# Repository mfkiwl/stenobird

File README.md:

# stenobird
a wip, unnamed stenographic keyboard family.
currently in a heavy WIP stage, with the repository acting as simple VC over the yamls and PCBs

## Design Considerations
The stenobird family aims to provide a **choc-spaced** and **variably choc min spaced** 222222+3 layout for stenography and standard typing.

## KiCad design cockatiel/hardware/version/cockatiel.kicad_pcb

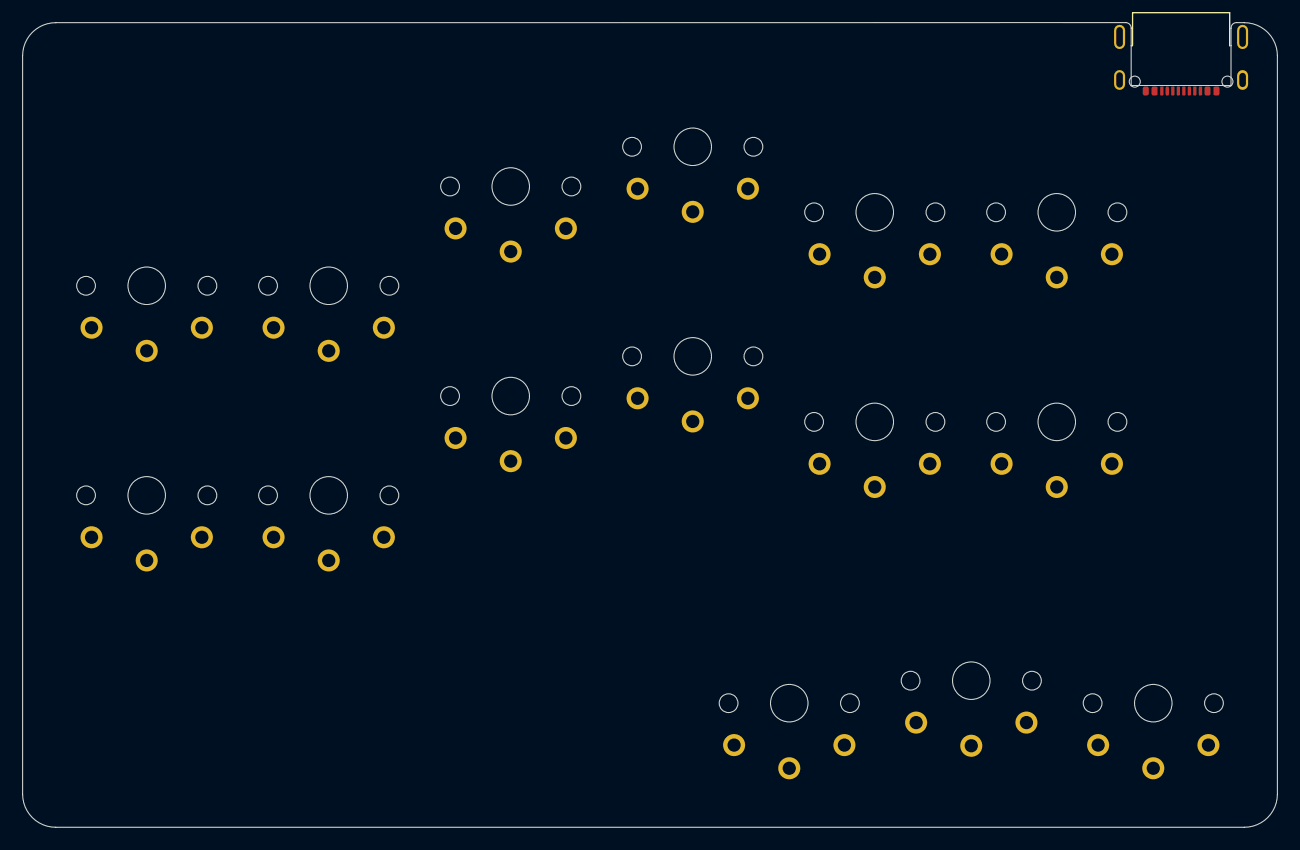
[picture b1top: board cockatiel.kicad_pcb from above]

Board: 4 copper layers, 113.8 x 72.9 mm, 17 parts (1 on the bottom side), 3 nets, no tracks yet.

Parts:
J1: USB_C_Receptacle_USB2.0; USB-C_MID_MOUNT_918-418K2024S40000
LOGO2: Logo_Open_Hardware_Small; OSHW_Logo_3.6x3.6_F.Mask
S1, S2, S3, S4, S5, S6, S7, S8, S9, S10, S11, S12, S13, S14, S15: pg1350-RS

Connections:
/USB+: J1.A6 (D+), J1.B6 (D+)
/USB-: J1.A7 (D-), J1.B7 (D-)
GND: J1.A1 (GND), J1.S1 (SHIELD), J1.S2 (SHIELD), J1.S3 (SHIELD), J1.S4 (SHIELD)

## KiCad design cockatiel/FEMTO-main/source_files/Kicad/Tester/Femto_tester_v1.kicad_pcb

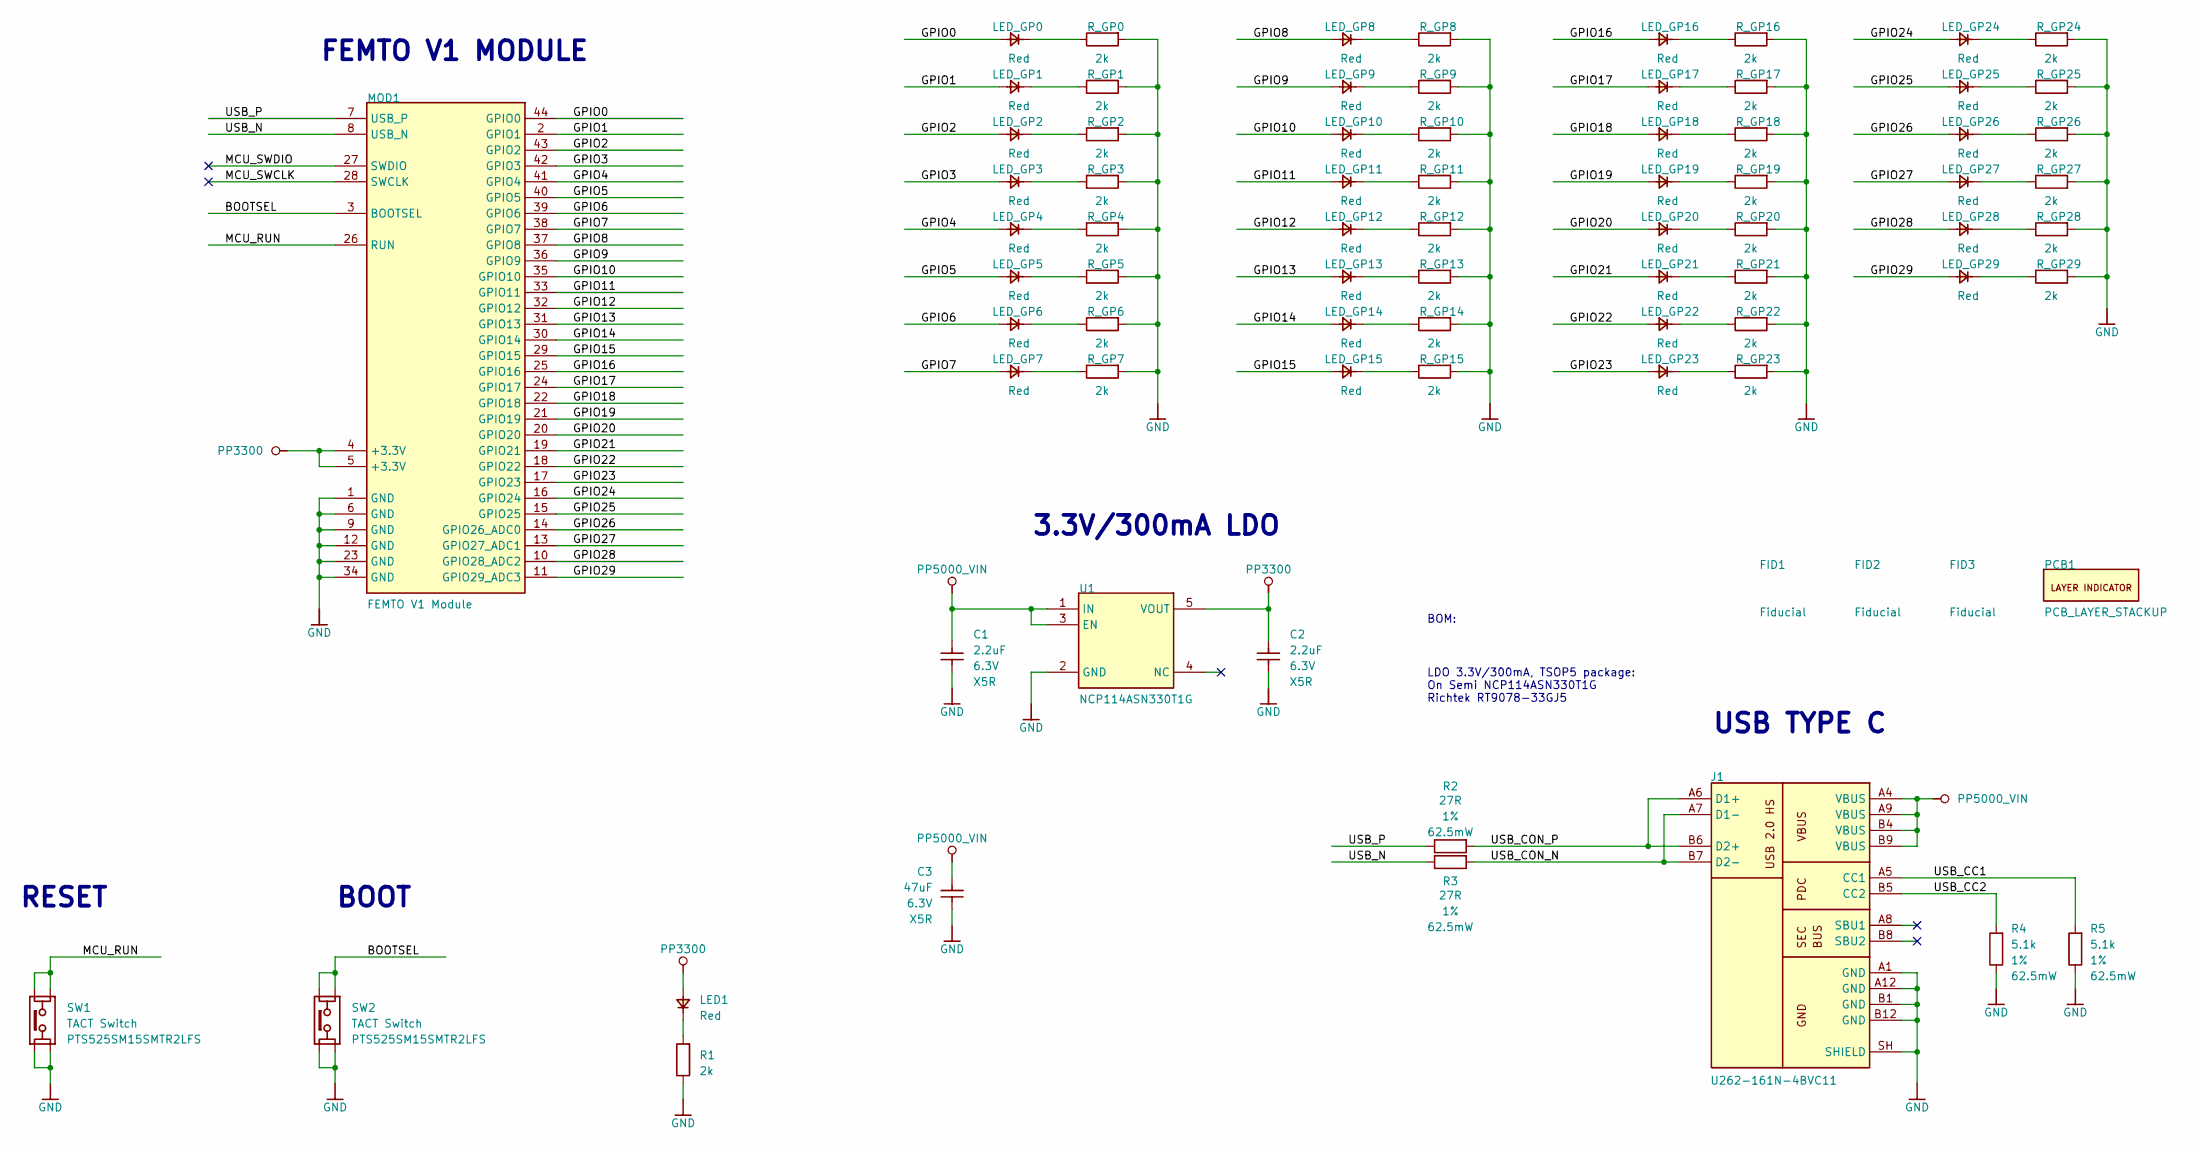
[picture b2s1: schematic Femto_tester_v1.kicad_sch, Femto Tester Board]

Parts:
C1, C2: 2.2uF; CAP_0402_R; VOLTAGE RATING 6.3V; TOLERANCE TBD; MPN CL05A225MQ5NNNC
C3: 47uF; CAP_0603_R; VOLTAGE RATING 6.3V; TOLERANCE TBD; MPN GENERIC
FID1, FID2, FID3: Fiducial; PCB_FID_RND_100x300
J1: U262-161N-4BVC11; CON_XKB_U262-161N-4BVC11; MPN U262-161N-4BVC11
LED1: Red; LED_0402_R
LED_GP0, LED_GP1, LED_GP2, LED_GP3, LED_GP4, LED_GP5, LED_GP6, LED_GP7, LED_GP8, LED_GP9, LED_GP10, LED_GP11, LED_GP12, LED_GP13, LED_GP14, LED_GP15, LED_GP16, LED_GP17, LED_GP18, LED_GP19, LED_GP20, LED_GP21, LED_GP22, LED_GP23, LED_GP24, LED_GP25, LED_GP26, LED_GP27, LED_GP28, LED_GP29: Red; LED_0402_R
MOD1: FEMTO V1 Module; _Biblioteki_MirFol_nowe_Pineberry_Lib.PcbLib_MOD_FEMTO_V1_1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
PCB1: PCB_LAYER_STACKUP; PCB_STACKUP-2L_A1
R1: 2k; RES_0402_R; TOLERANCE 1%; POWER RATING 62.5mW; MPN RC0402FR-072KP
R2, R3: 27R; RES_0402_R; TOLERANCE 1%; POWER RATING 62.5mW; MPN RC0402FR-0727RL
R4, R5: 5.1k; RES_0402_R; TOLERANCE 1%; POWER RATING 62.5mW; MPN RC0402FR-075K1L
R_GP0, R_GP1, R_GP2, R_GP3, R_GP4, R_GP5, R_GP6, R_GP7, R_GP8, R_GP9, R_GP10, R_GP11, R_GP12, R_GP13, R_GP14, R_GP15, R_GP16, R_GP17, R_GP18, R_GP19, R_GP20, R_GP21, R_GP22, R_GP23, R_GP24, R_GP25, R_GP26, R_GP27, R_GP28, R_GP29: 2k; RES_0402_R; TOLERANCE 1%; POWER RATING 62.5mW; MPN RC0402FR-072KP
SW1, SW2: TACT Switch; SWI_CKS_PTS525; MPN PTS525SM15SMTR2LFS
U1: NCP114ASN330T1G; _Biblioteki_MirFol_nowe_SH_lib.PcbLib_ICC_TSOT-5_290X160H11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; MPN NCP114ASN330T1G

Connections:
/BOOTSEL: MOD1.3 (BOOTSEL), SW2.1, SW2.2
/GPIO0: LED_GP0.2, MOD1.44 (GPIO0)
/GPIO1: LED_GP1.2, MOD1.2 (GPIO1)
/GPIO2: LED_GP2.2, MOD1.43 (GPIO2)
/GPIO3: LED_GP3.2, MOD1.42 (GPIO3)
/GPIO4: LED_GP4.2, MOD1.41 (GPIO4)
/GPIO5: LED_GP5.2, MOD1.40 (GPIO5)
/GPIO6: LED_GP6.2, MOD1.39 (GPIO6)
/GPIO7: LED_GP7.2, MOD1.38 (GPIO7)
/GPIO8: LED_GP8.2, MOD1.37 (GPIO8)
/GPIO9: LED_GP9.2, MOD1.36 (GPIO9)
/GPIO10: LED_GP10.2, MOD1.35 (GPIO10)
/GPIO11: LED_GP11.2, MOD1.33 (GPIO11)
/GPIO12: LED_GP12.2, MOD1.32 (GPIO12)
/GPIO13: LED_GP13.2, MOD1.31 (GPIO13)
/GPIO14: LED_GP14.2, MOD1.30 (GPIO14)
/GPIO15: LED_GP15.2, MOD1.29 (GPIO15)
/GPIO16: LED_GP16.2, MOD1.25 (GPIO16)
/GPIO17: LED_GP17.2, MOD1.24 (GPIO17)
/GPIO18: LED_GP18.2, MOD1.22 (GPIO18)
/GPIO19: LED_GP19.2, MOD1.21 (GPIO19)
/GPIO20: LED_GP20.2, MOD1.20 (GPIO20)
/GPIO21: LED_GP21.2, MOD1.19 (GPIO21)
/GPIO22: LED_GP22.2, MOD1.18 (GPIO22)
/GPIO23: LED_GP23.2, MOD1.17 (GPIO23)
/GPIO24: LED_GP24.2, MOD1.16 (GPIO24)
/GPIO25: LED_GP25.2, MOD1.15 (GPIO25)
/GPIO26: LED_GP26.2, MOD1.14 (GPIO26_ADC0)
/GPIO27: LED_GP27.2, MOD1.13 (GPIO27_ADC1)
/GPIO28: LED_GP28.2, MOD1.10 (GPIO28_ADC2)
/GPIO29: LED_GP29.2, MOD1.11 (GPIO29_ADC3)
/MCU_RUN: MOD1.26 (RUN), SW1.1, SW1.2
/MCU_SWCLK: MOD1.28 (SWCLK)
/MCU_SWDIO: MOD1.27 (SWDIO)
/USB_CC1: J1.A5 (CC1), R5.2
/USB_CC2: J1.B5 (CC2), R4.2
/USB_CON_N: J1.A7 (D1-), J1.B7 (D2-), R3.2
/USB_CON_P: J1.A6 (D1+), J1.B6 (D2+), R2.2
/USB_N: MOD1.8 (USB_N), R3.1
/USB_P: MOD1.7 (USB_P), R2.1
GND: C1.1, C2.1, C3.1, J1.A1 (GND), J1.A12 (GND), J1.B1 (GND), J1.B12 (GND), J1.SH (SHIELD), MOD1.1 (GND), MOD1.6 (GND), MOD1.9 (GND), MOD1.12 (GND), MOD1.23 (GND), MOD1.34 (GND), R1.1, R4.1, R5.1, R_GP0.1, R_GP1.1, R_GP2.1, R_GP3.1, R_GP4.1, R_GP5.1, R_GP6.1, R_GP7.1, R_GP8.1, R_GP9.1, R_GP10.1, R_GP11.1, R_GP12.1, R_GP13.1, R_GP14.1, R_GP15.1, R_GP16.1, R_GP17.1, R_GP18.1, R_GP19.1, R_GP20.1, R_GP21.1, R_GP22.1, R_GP23.1, R_GP24.1, R_GP25.1, R_GP26.1, R_GP27.1, R_GP28.1, R_GP29.1, SW1.3, SW1.4, SW2.3, SW2.4, U1.2 (GND)
unnamed: LED1.1, R1.2
unnamed: LED_GP0.1, R_GP0.2
unnamed: LED_GP1.1, R_GP1.2
unnamed: LED_GP2.1, R_GP2.2
unnamed: LED_GP3.1, R_GP3.2
unnamed: LED_GP4.1, R_GP4.2
unnamed: LED_GP5.1, R_GP5.2
unnamed: LED_GP6.1, R_GP6.2
unnamed: LED_GP7.1, R_GP7.2
unnamed: LED_GP8.1, R_GP8.2
unnamed: LED_GP9.1, R_GP9.2
unnamed: LED_GP10.1, R_GP10.2
unnamed: LED_GP11.1, R_GP11.2
unnamed: LED_GP12.1, R_GP12.2
unnamed: LED_GP13.1, R_GP13.2
unnamed: LED_GP14.1, R_GP14.2
unnamed: LED_GP15.1, R_GP15.2
unnamed: LED_GP16.1, R_GP16.2
unnamed: LED_GP17.1, R_GP17.2
unnamed: LED_GP18.1, R_GP18.2
unnamed: LED_GP19.1, R_GP19.2
unnamed: LED_GP20.1, R_GP20.2
unnamed: LED_GP21.1, R_GP21.2
unnamed: LED_GP22.1, R_GP22.2
unnamed: LED_GP23.1, R_GP23.2
unnamed: LED_GP24.1, R_GP24.2
unnamed: LED_GP25.1, R_GP25.2
unnamed: LED_GP26.1, R_GP26.2
unnamed: LED_GP27.1, R_GP27.2
unnamed: LED_GP28.1, R_GP28.2
unnamed: LED_GP29.1, R_GP29.2
PP3300: C2.2, LED1.2, MOD1.4 (+3.3V), MOD1.5 (+3.3V), U1.5 (VOUT)
PP5000_VIN: C1.2, C3.2, J1.A4 (VBUS), J1.A9 (VBUS), J1.B4 (VBUS), J1.B9 (VBUS), U1.1 (IN), U1.3 (EN)

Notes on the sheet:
BOM:
USB TYPE C
BOOT
3.3V/300mA LDO
FEMTO V1 MODULE
RESET
LDO 3.3V/300mA, TSOP5 package: On Semi NCP114ASN330T1G Richtek RT9078-33GJ5

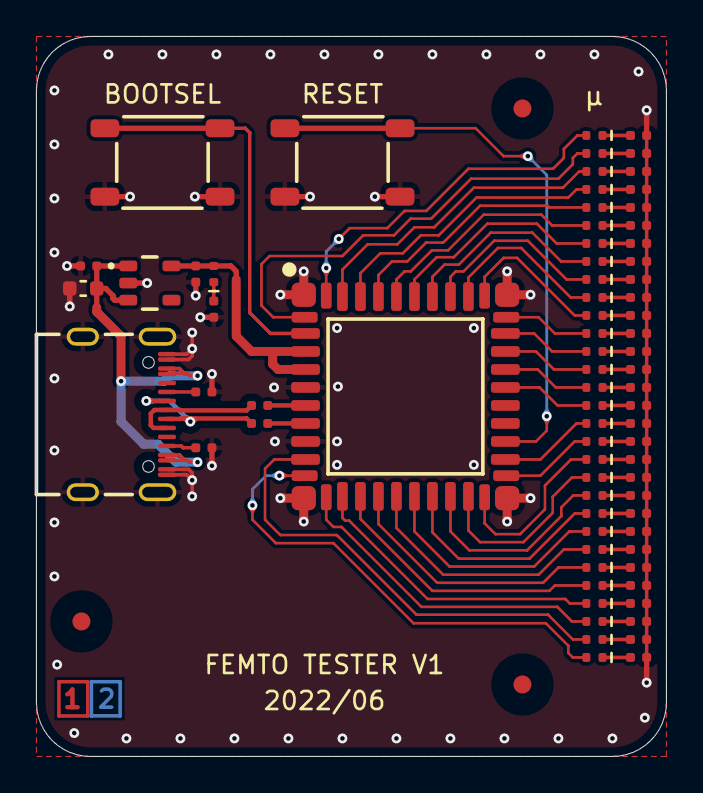
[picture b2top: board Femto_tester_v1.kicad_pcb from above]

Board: 2 copper layers, 35.0 x 40.0 mm, 78 parts (0 on the bottom side), 72 nets.

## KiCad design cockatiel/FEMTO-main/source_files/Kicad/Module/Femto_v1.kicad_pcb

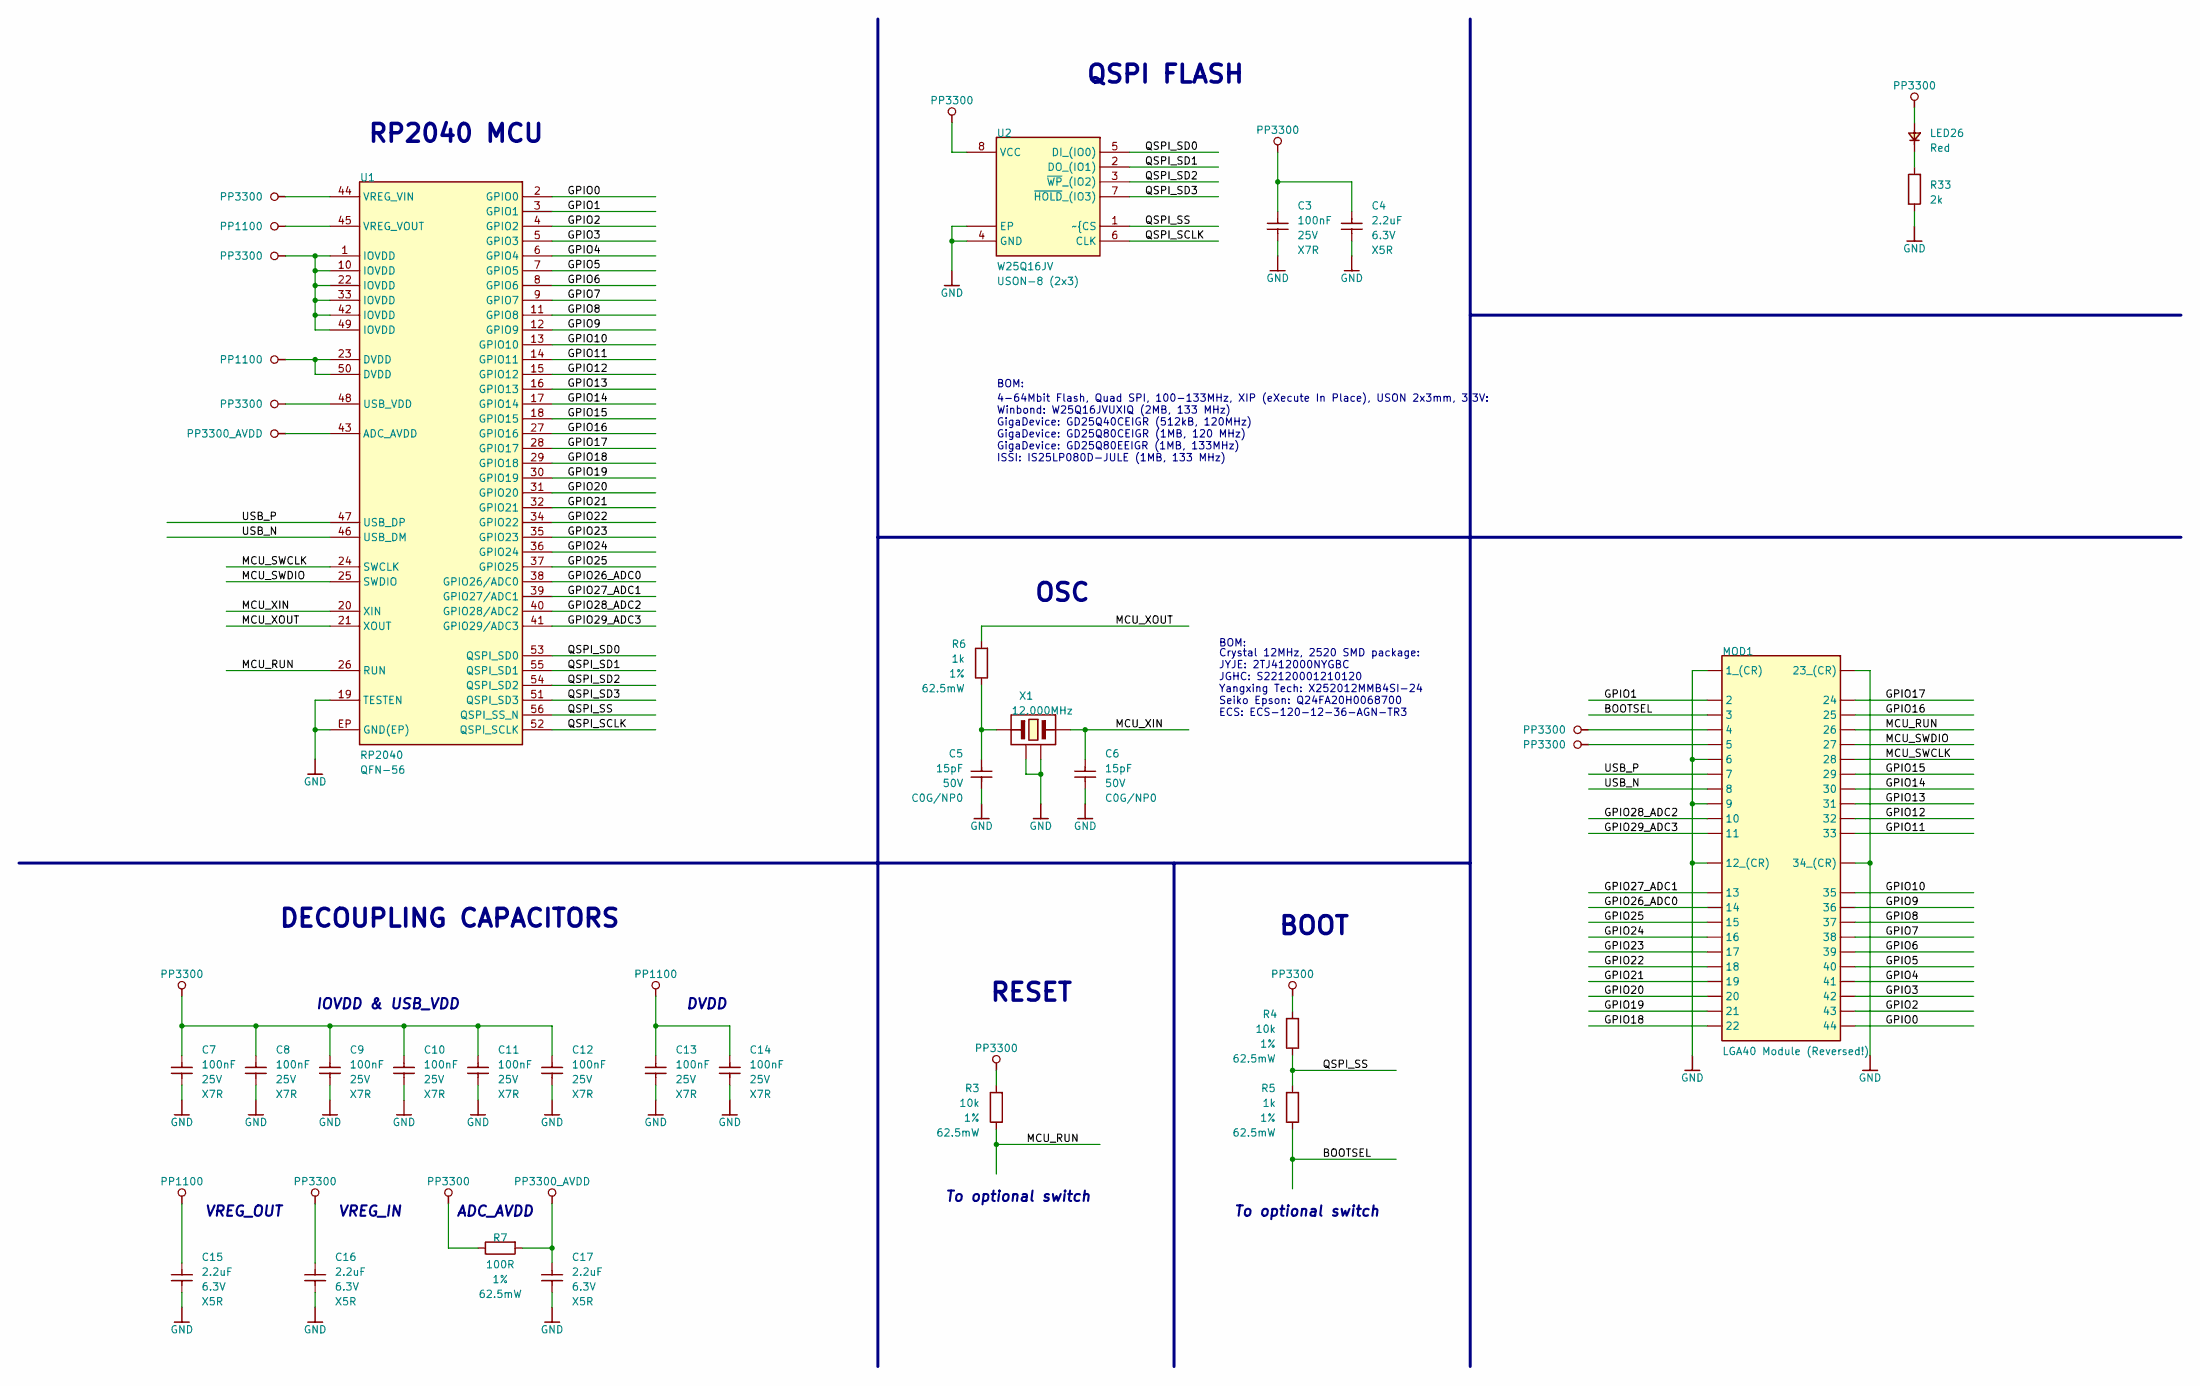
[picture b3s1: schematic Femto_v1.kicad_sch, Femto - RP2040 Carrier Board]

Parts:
C3, C7, C8, C9, C10, C11, C12, C13, C14: 100nF; CAP_0402_R; VOLTAGE RATING 25V; TOLERANCE TBD; MPN CL05B104KA5NNNC
C4, C15, C16, C17: 2.2uF; CAP_0402_R; VOLTAGE RATING 6.3V; TOLERANCE TBD; MPN CL05A225MQ5NNNC
C5, C6: 15pF; CAP_0402_R; VOLTAGE RATING 50V; TOLERANCE TBD; MPN C0402C150J5GACTU
LED26: Red; LED_0402_R
MOD1: LGA40 Module (Reversed!); PCB_LGA40_120X120_P100_REV
R3, R4: 10k; RES_0402_R; TOLERANCE 1%; POWER RATING 62.5mW; MPN RC0402FR-0710KL
R5, R6: 1k; RES_0402_R; TOLERANCE 1%; POWER RATING 62.5mW; MPN RC0402FR-071KL
R7: 100R; RES_0402_R; TOLERANCE 1%; POWER RATING 62.5mW; MPN RC0402FR-07100RL
R33: 2k; RES_0402_R; TOLERANCE 1%; POWER RATING 62.5mW; MPN RC0402FR-072KP
U1: RP2040; ICC_QFN56_700X700X90_P40_EP_RP2040; MPN RP2040
U2: W25Q16JV; ICC_USON8_200X300X55P50_EP; MPN W25Q16JVUXIQ
X1: 12.000MHz; OSC_2520_4P_250X200H50_R; MPN ECS-120-12-36-AGN-TR3

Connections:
/BOOTSEL: MOD1.3, R5.1
/GPIO0: MOD1.44, U1.2 (GPIO0)
/GPIO1: MOD1.2, U1.3 (GPIO1)
/GPIO2: MOD1.43, U1.4 (GPIO2)
/GPIO3: MOD1.42, U1.5 (GPIO3)
/GPIO4: MOD1.41, U1.6 (GPIO4)
/GPIO5: MOD1.40, U1.7 (GPIO5)
/GPIO6: MOD1.39, U1.8 (GPIO6)
/GPIO7: MOD1.38, U1.9 (GPIO7)
/GPIO8: MOD1.37, U1.11 (GPIO8)
/GPIO9: MOD1.36, U1.12 (GPIO9)
/GPIO10: MOD1.35, U1.13 (GPIO10)
/GPIO11: MOD1.33, U1.14 (GPIO11)
/GPIO12: MOD1.32, U1.15 (GPIO12)
/GPIO13: MOD1.31, U1.16 (GPIO13)
/GPIO14: MOD1.30, U1.17 (GPIO14)
/GPIO15: MOD1.29, U1.18 (GPIO15)
/GPIO16: MOD1.25, U1.27 (GPIO16)
/GPIO17: MOD1.24, U1.28 (GPIO17)
/GPIO18: MOD1.22, U1.29 (GPIO18)
/GPIO19: MOD1.21, U1.30 (GPIO19)
/GPIO20: MOD1.20, U1.31 (GPIO20)
/GPIO21: MOD1.19, U1.32 (GPIO21)
/GPIO22: MOD1.18, U1.34 (GPIO22)
/GPIO23: MOD1.17, U1.35 (GPIO23)
/GPIO24: MOD1.16, U1.36 (GPIO24)
/GPIO25: MOD1.15, U1.37 (GPIO25)
/GPIO26_ADC0: MOD1.14, U1.38 (GPIO26/ADC0)
/GPIO27_ADC1: MOD1.13, U1.39 (GPIO27/ADC1)
/GPIO28_ADC2: MOD1.10, U1.40 (GPIO28/ADC2)
/GPIO29_ADC3: MOD1.11, U1.41 (GPIO29/ADC3)
/MCU_RUN: MOD1.26, R3.1, U1.26 (RUN)
/MCU_SWCLK: MOD1.28, U1.24 (SWCLK)
/MCU_SWDIO: MOD1.27, U1.25 (SWDIO)
/MCU_XIN: C6.2, U1.20 (XIN), X1.3
/MCU_XOUT: R6.1, U1.21 (XOUT)
/QSPI_SCLK: U1.52 (QSPI_SCLK), U2.6 (CLK)
/QSPI_SD0: U1.53 (QSPI_SD0), U2.5 (DI_(IO0))
/QSPI_SD1: U1.55 (QSPI_SD1), U2.2 (DO_(IO1))
/QSPI_SD2: U1.54 (QSPI_SD2), U2.3 (~WP_(IO2))
/QSPI_SD3: U1.51 (QSPI_SD3), U2.7 (~HOLD_(IO3))
/QSPI_SS: R4.1, R5.2, U1.56 (QSPI_SS_N), U2.1 (~{CS)
/USB_N: MOD1.8, U1.46 (USB_DM)
/USB_P: MOD1.7, U1.47 (USB_DP)
GND: C3.1, C4.1, C5.1, C6.1, C7.1, C8.1, C9.1, C10.1, C11.1, C12.1, C13.1, C14.1, C15.1, C16.1, C17.1, MOD1.1 (1_(CR)), MOD1.6, MOD1.9, MOD1.12 (12_(CR)), MOD1.23 (23_(CR)), MOD1.34 (34_(CR)), R33.1, U1.19 (TESTEN), U1.EP (GND(EP)), U2.4 (GND), U2.EP, X1.2, X1.4
unnamed: C5.2, R6.2, X1.1
unnamed: LED26.1, R33.2
PP1100: C13.2, C14.2, C15.2, U1.23 (DVDD), U1.45 (VREG_VOUT), U1.50 (DVDD)
PP3300: C3.2, C4.2, C7.2, C8.2, C9.2, C10.2, C11.2, C12.2, C16.2, LED26.2, MOD1.4, MOD1.5, R3.2, R4.2, R7.2, U1.1 (IOVDD), U1.10 (IOVDD), U1.22 (IOVDD), U1.33 (IOVDD), U1.42 (IOVDD), U1.44 (VREG_VIN), U1.48 (USB_VDD), U1.49 (IOVDD), U2.8 (VCC)
PP3300_AVDD: C17.2, R7.1, U1.43 (ADC_AVDD)

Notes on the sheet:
To optional switch
ADC_AVDD
OSC
VREG_IN
RP2040 MCU
VREG_OUT
DVDD
IOVDD & USB_VDD
BOOT
QSPI FLASH
BOM:
4-64Mbit Flash, Quad SPI, 100-133MHz, XIP (eXecute In Place), USON 2x3mm, 3.3V: Winbond: W25Q16JVUXIQ (2MB, 133 MHz) GigaDevice: GD25Q40CEIGR (512kB, 120MHz) GigaDevice: GD25Q80CEIGR (1MB, 120 MHz) GigaDevice: GD25Q80EEIGR (1MB, 133MHz) ISSI: IS25LP080D-JULE (1MB, 133 MHz)
Crystal 12MHz, 2520 SMD package: JYJE: 2TJ412000NYGBC JGHC: S22120001210120 Yangxing Tech: X252012MMB4SI-24 Seiko Epson: Q24FA20H0068700 ECS: ECS-120-12-36-AGN-TR3
DECOUPLING CAPACITORS
RESET

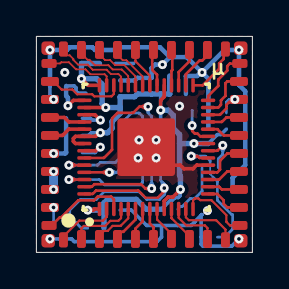
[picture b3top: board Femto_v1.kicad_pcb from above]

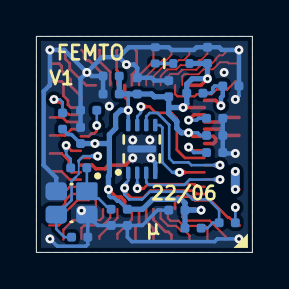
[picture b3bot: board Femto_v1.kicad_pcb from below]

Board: 4 copper layers, 12.0 x 12.0 mm, 26 parts (24 on the bottom side), 50 nets.

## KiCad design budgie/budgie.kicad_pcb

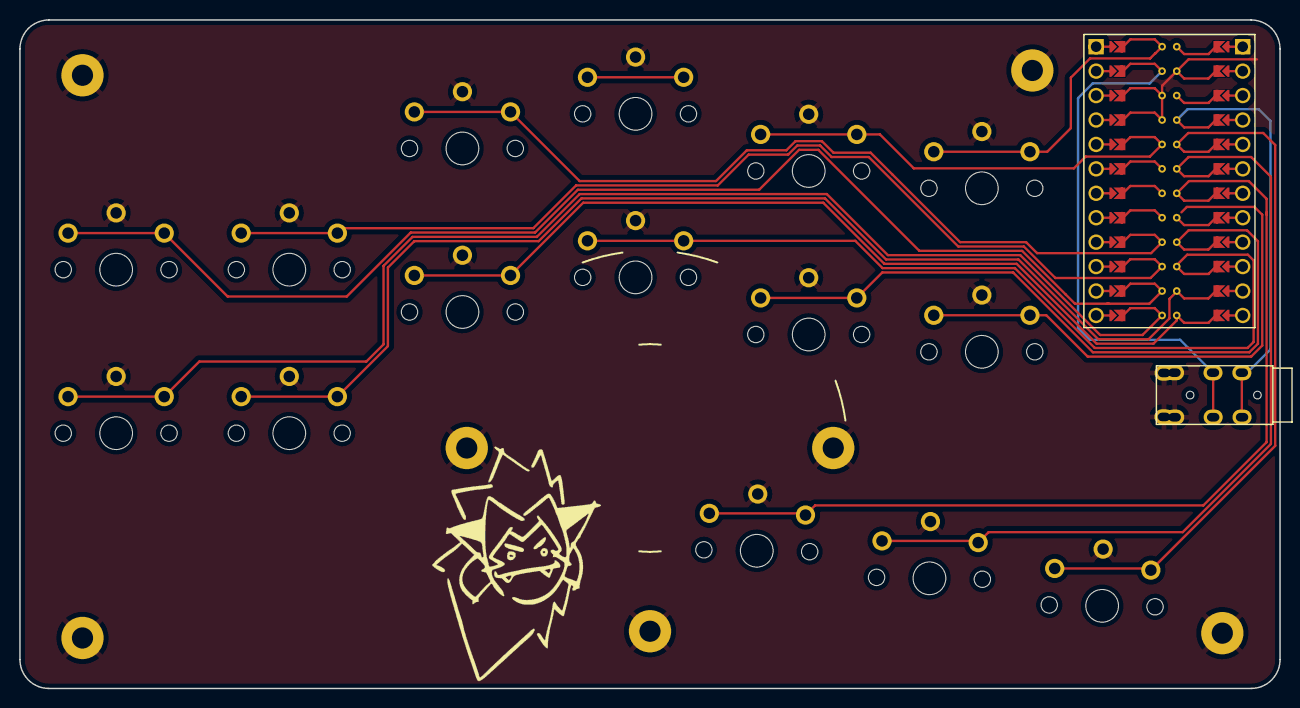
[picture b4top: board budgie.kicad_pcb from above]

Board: 2 copper layers, 131.0 x 69.5 mm, 19 parts (1 on the bottom side), 17 nets.

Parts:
J2: AudioJack4dpb; TRRS-PJ-DPB2
Ref**: Val**; catra
Ref**#2: Val**; adora
S1, S2, S3, S4, S5, S6, S7, S8, S9, S10, S11, S12, S13, S14, S15: pg1350-R
U1: ProMicro-kbd; ProMicro_jumpers_facedown

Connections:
GND: J2.S, J2.T, S1.1, S2.1, S3.1, S4.1, S5.1, S6.1, S7.1, S8.1, S9.1, S10.1, S11.1, S12.1, S13.1, S14.1, S15.1, U1.3, U1.4, U1.23
RX: J2.R1, U1.2
VCC: J2.R2, U1.21
matrix_index_bottom: S9.2, U1.16
matrix_index_home: S10.2, U1.5
matrix_inner_bottom: S11.2, U1.17
matrix_inner_home: S12.2, U1.1
matrix_middle_bottom: S7.2, U1.15
matrix_outer_bottom: S1.2, U1.12
matrix_outer_home: S2.2, U1.11
matrix_pinky_bottom: S3.2, U1.14
matrix_pinky_home: S4.2, U1.10
matrix_ring_bottom: S5.2, U1.13
matrix_ring_home: S6.2, U1.9
thumb_homey: S14.2, U1.19
thumb_reachy: S15.2, U1.20
thumb_tucky: S13.2, U1.18

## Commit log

2022-08-11 init
2022-08-11 rename
2022-08-12 init pcb
2022-08-12 wobbly edge cuts
2022-08-25 commit bc im formatting my pc lol
